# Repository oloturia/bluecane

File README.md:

# bluecane
Dog finder, sketch for Arduino

It transfers latitude and longitude via Bluetooth to a device.

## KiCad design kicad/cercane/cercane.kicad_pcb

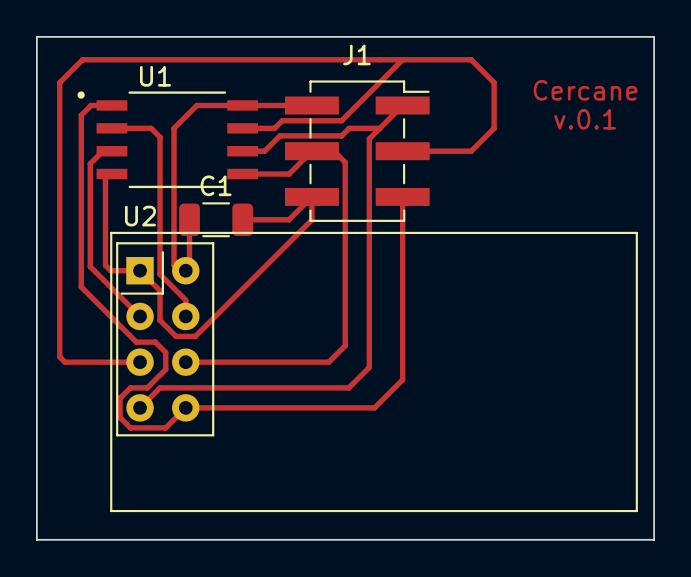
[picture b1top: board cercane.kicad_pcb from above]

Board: 2 copper layers, 34.3 x 27.9 mm, 4 parts (0 on the bottom side), 8 nets.

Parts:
C1: 100nF; C_1206_3216Metric
J1: Conn_02x03_Odd_Even; PinSocket_2x03_P2.54mm_Vertical_SMD
U1: ATtiny45-20PU; SOIC127P798X216-8N
U2: NRF24L01_Breakout; nRF24L01_Breakout

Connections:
+3V3: C1.1, J1.2, U1.8, U2.2
/MISO: J1.1, U1.6, U2.7
/MOSI: J1.4, U1.5, U2.6
/RST: J1.5, U1.1, U2.8
/SCK: J1.3, U1.7, U2.5
GND: C1.2, J1.6, U1.4, U2.1
unnamed: U1.2, U2.4
unnamed: U1.3, U2.3

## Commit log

2015-03-05 corrected wordwrap
2015-03-06 fixing serial concurrency
2015-03-16 fixed syntax
2015-03-18 added raw output from gps and string example
2015-03-25 added + sign to lat & long
2015-10-12 Create LICENSE
2021-05-31 3D model
2021-05-31 removed useless sketch
2021-06-02 forgot cover
2021-06-03 Added giraSoul solar orientator
2021-07-07 cleaned up
2021-07-07 new PCB
2021-07-15 new components on PCB
2021-07-27 Exported PCB in png and svg
2021-07-28 combed tracks
